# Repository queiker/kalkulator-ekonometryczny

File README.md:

# kalkulator-ekonometryczny
projetk kalkulatora który będzie miał funkcje niedostępne w urządzeniach dostępnych w sklepach
będzie liczył procent składany , będzie miał funkcje prognozy metodą najmniejszych kwadratów

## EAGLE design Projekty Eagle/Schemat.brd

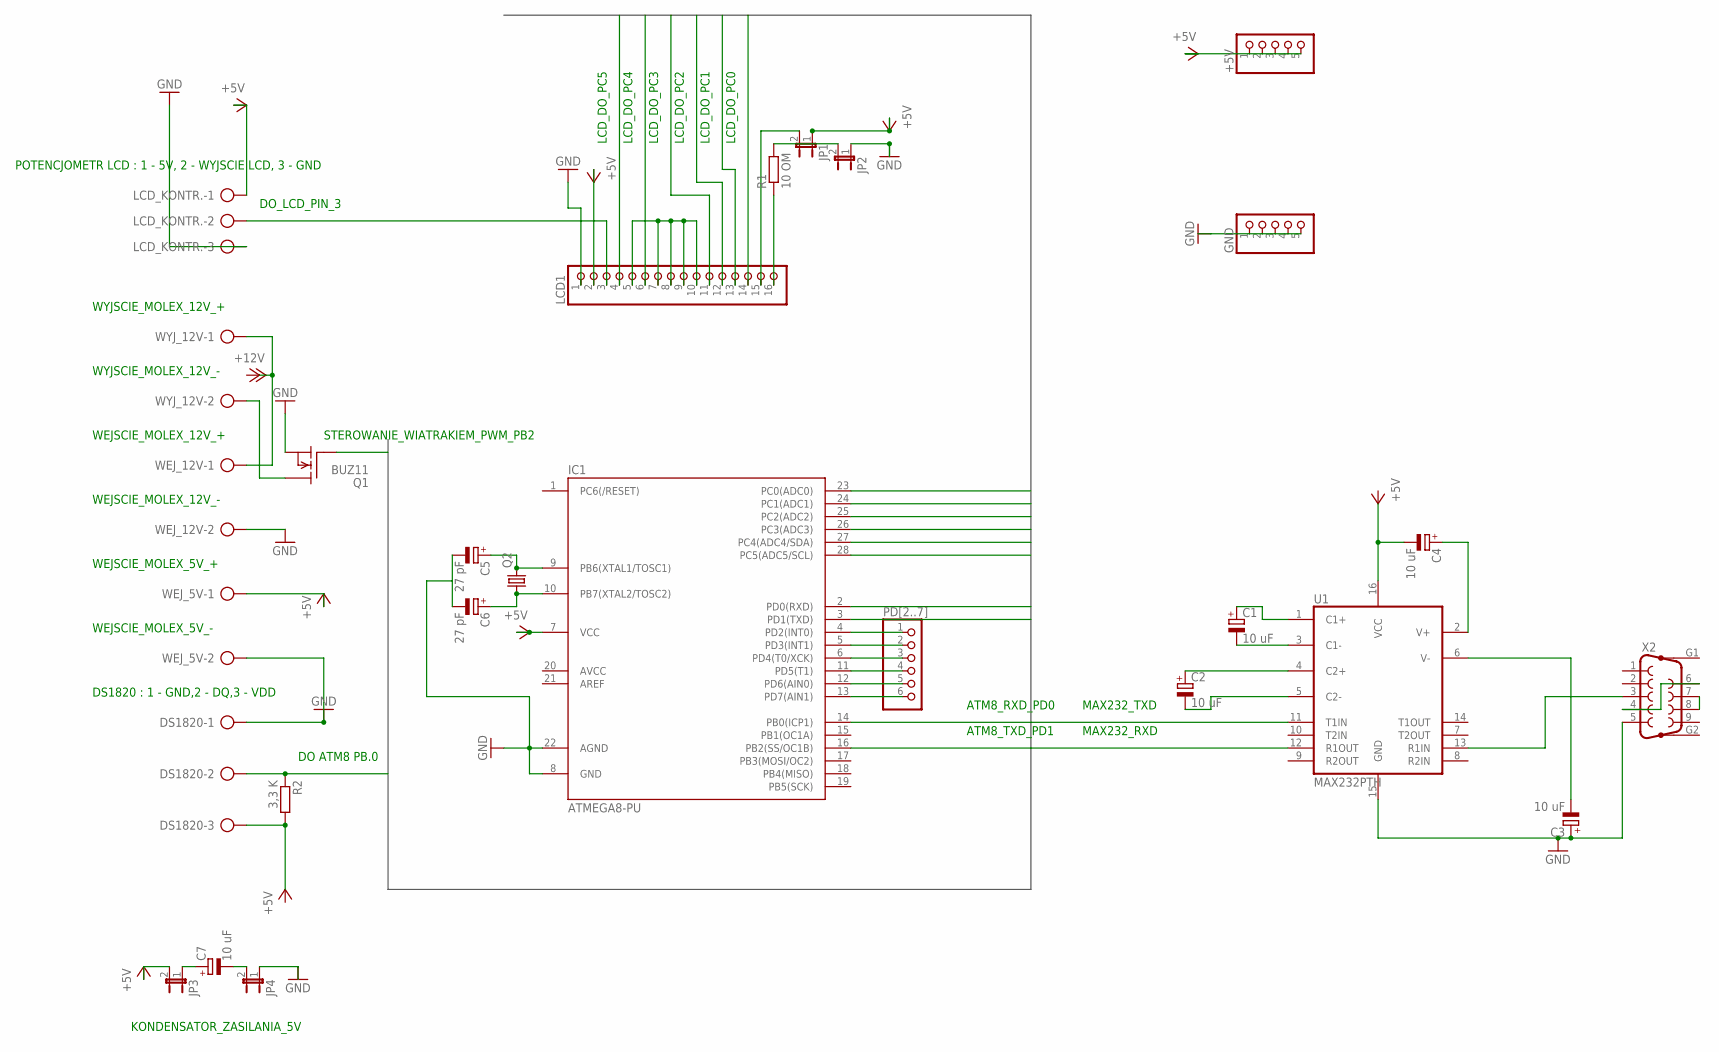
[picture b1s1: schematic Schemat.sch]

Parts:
+5V: PINHD-1X5; 1X05
C1, C2, C3, C4, C7: 10 uF; E5-10,5
C5, C6: 27 pF; E5-10,5
DS1820: AK500/3-H
GND: PINHD-1X5; 1X05
IC1: ATMEGA8-PU; DIL28-3
JP1, JP2, JP3, JP4: JP1E; JP1
LCD1: PINHD-1X16; 1X16
LCD_KONTR.: AK500/3-H
PD[2..7]: PINHD-1X6; 1X06
Q1: BUZ11; TO220
Q2: CRYSTALHC49S; HC49/S
R1: 10 OM; 0207/15
R2: 3,3 K; 0207/15
U1: MAX232PTH; DIL16
WEJ_5V, WEJ_12V: AK500/2-H
WYJ_12V: AK500/2-H
X2: F09HP

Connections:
+5V: +5V.1, +5V.2, +5V.3, +5V.4, +5V.5, IC1.7 (VCC), JP1.1, JP3.2, LCD1.2, LCD_KONTR..1, WEJ_5V.1
GND: C3.+, C5.-, C6.-, DS1820.1, GND.1, GND.2, GND.3, GND.4, GND.5, IC1.8 (GND), IC1.22 (AGND), JP2.1, JP4.1, LCD1.1, LCD_KONTR..3, Q1.3 (S), U1.15 (GND), WEJ_5V.2, WEJ_12V.2, X2.5
unnamed: C1.-, U1.3 (C1-)
unnamed: C1.+, U1.1 (C1+)
unnamed: C2.+, U1.4 (C2+)
unnamed: C2.-, U1.5 (C2-)
unnamed: X2.4, X2.6
unnamed: X2.7, X2.8
unnamed: U1.13 (R1IN), X2.3
unnamed: C4.-, U1.16 (VCC)
unnamed: C3.-, U1.6 (V-)
unnamed: C4.+, U1.2 (V+)
unnamed: C7.+, JP3.1
unnamed: C7.-, JP4.2
unnamed: IC1.4 (PD2(INT0)), PD[2..7].1
unnamed: IC1.5 (PD3(INT1)), PD[2..7].2
unnamed: DS1820.3, R2.2
unnamed: IC1.6 (PD4(T0/XCK)), PD[2..7].3
unnamed: LCD1.3, LCD_KONTR..2
unnamed: WEJ_12V.1, WYJ_12V.1
unnamed: IC1.11 (PD5(T1)), PD[2..7].4
unnamed: Q1.2 (D), WYJ_12V.2
unnamed: LCD1.5, LCD1.7, LCD1.8, LCD1.9, LCD1.10
unnamed: IC1.12 (PD6(AIN0)), PD[2..7].5
unnamed: C5.+, IC1.9 (PB6(XTAL1/TOSC1)), Q2.2
unnamed: IC1.13 (PD7(AIN1)), PD[2..7].6
unnamed: JP1.2, LCD1.15
unnamed: JP2.2, R1.2
unnamed: C6.+, IC1.10 (PB7(XTAL2/TOSC2)), Q2.1
unnamed: LCD1.16, R1.1
PB0: DS1820.2, IC1.14 (PB0(ICP1)), R2.1
PB2: IC1.16 (PB2(SS/OC1B)), Q1.1 (G)
PC0: IC1.23 (PC0(ADC0)), LCD1.14
PC1: IC1.24 (PC1(ADC1)), LCD1.13
PC2: IC1.25 (PC2(ADC2)), LCD1.12
PC3: IC1.26 (PC3(ADC3)), LCD1.11
PC4: IC1.27 (PC4(ADC4/SDA)), LCD1.6
PC5: IC1.28 (PC5(ADC5/SCL)), LCD1.4
PD0: IC1.2 (PD0(RXD)), U1.11 (T1IN)
PD1: IC1.3 (PD1(TXD)), U1.12 (R1OUT)

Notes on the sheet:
MAX232_TXD
MAX232_RXD
WEJSCIE_MOLEX_12V_+
WEJSCIE_MOLEX_12V_-
WEJSCIE_MOLEX_5V_+
WEJSCIE_MOLEX_5V_-
DS1820 : 1 - GND,2 - DQ,3 - VDD
ATM8_RXD_PD0
ATM8_TXD_PD1
POTENCJOMETR LCD : 1 - 5V, 2 - WYJSCIE LCD, 3 - GND
DO ATM8 PB.0
WYJSCIE_MOLEX_12V_+
WYJSCIE_MOLEX_12V_-
STEROWANIE_WIATRAKIEM_PWM_PB2
DO_LCD_PIN_3
LCD_DO_PC5
LCD_DO_PC4
LCD_DO_PC3
LCD_DO_PC2
LCD_DO_PC1
LCD_DO_PC0
KONDENSATOR_ZASILANIA_5V

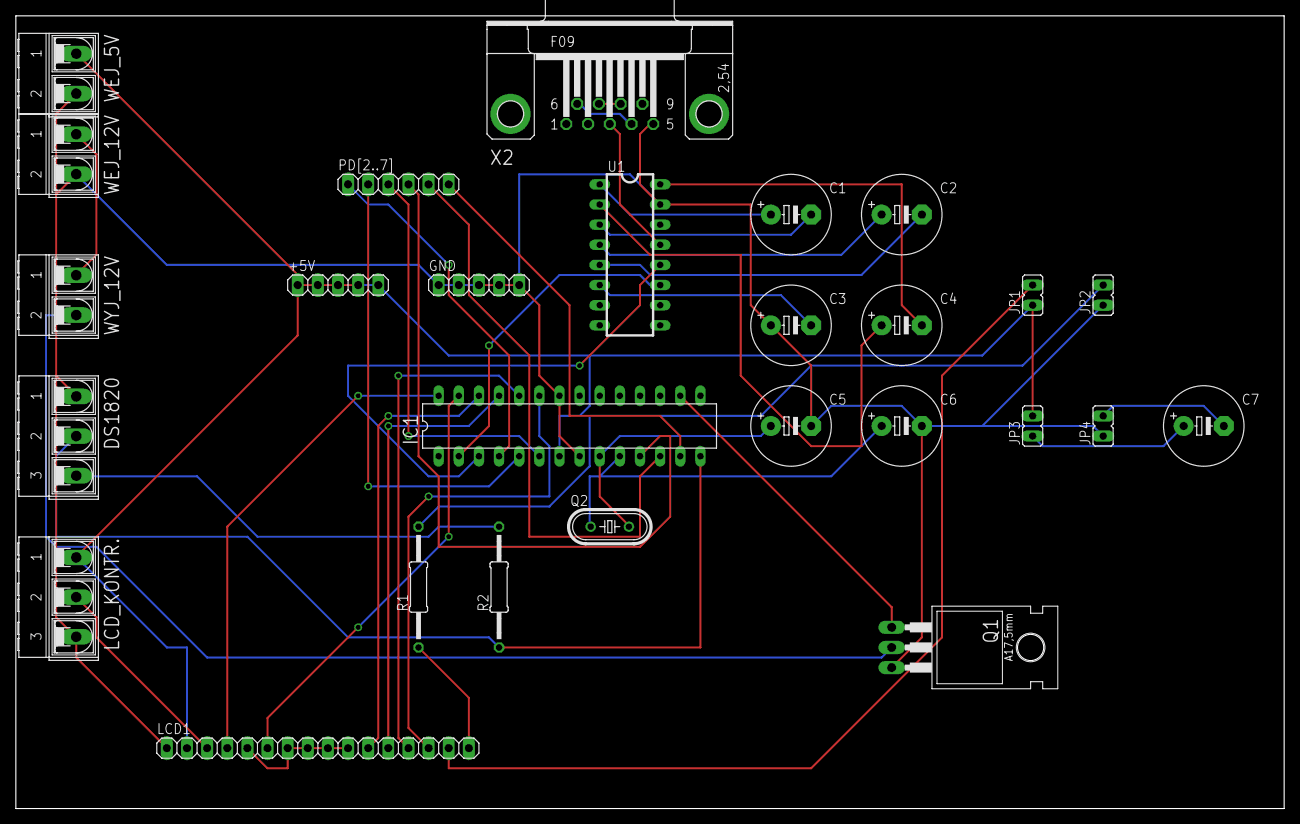
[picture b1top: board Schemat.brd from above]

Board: 2 copper layers, 160.0 x 100.0 mm, 27 parts (0 on the bottom side), 40 nets.

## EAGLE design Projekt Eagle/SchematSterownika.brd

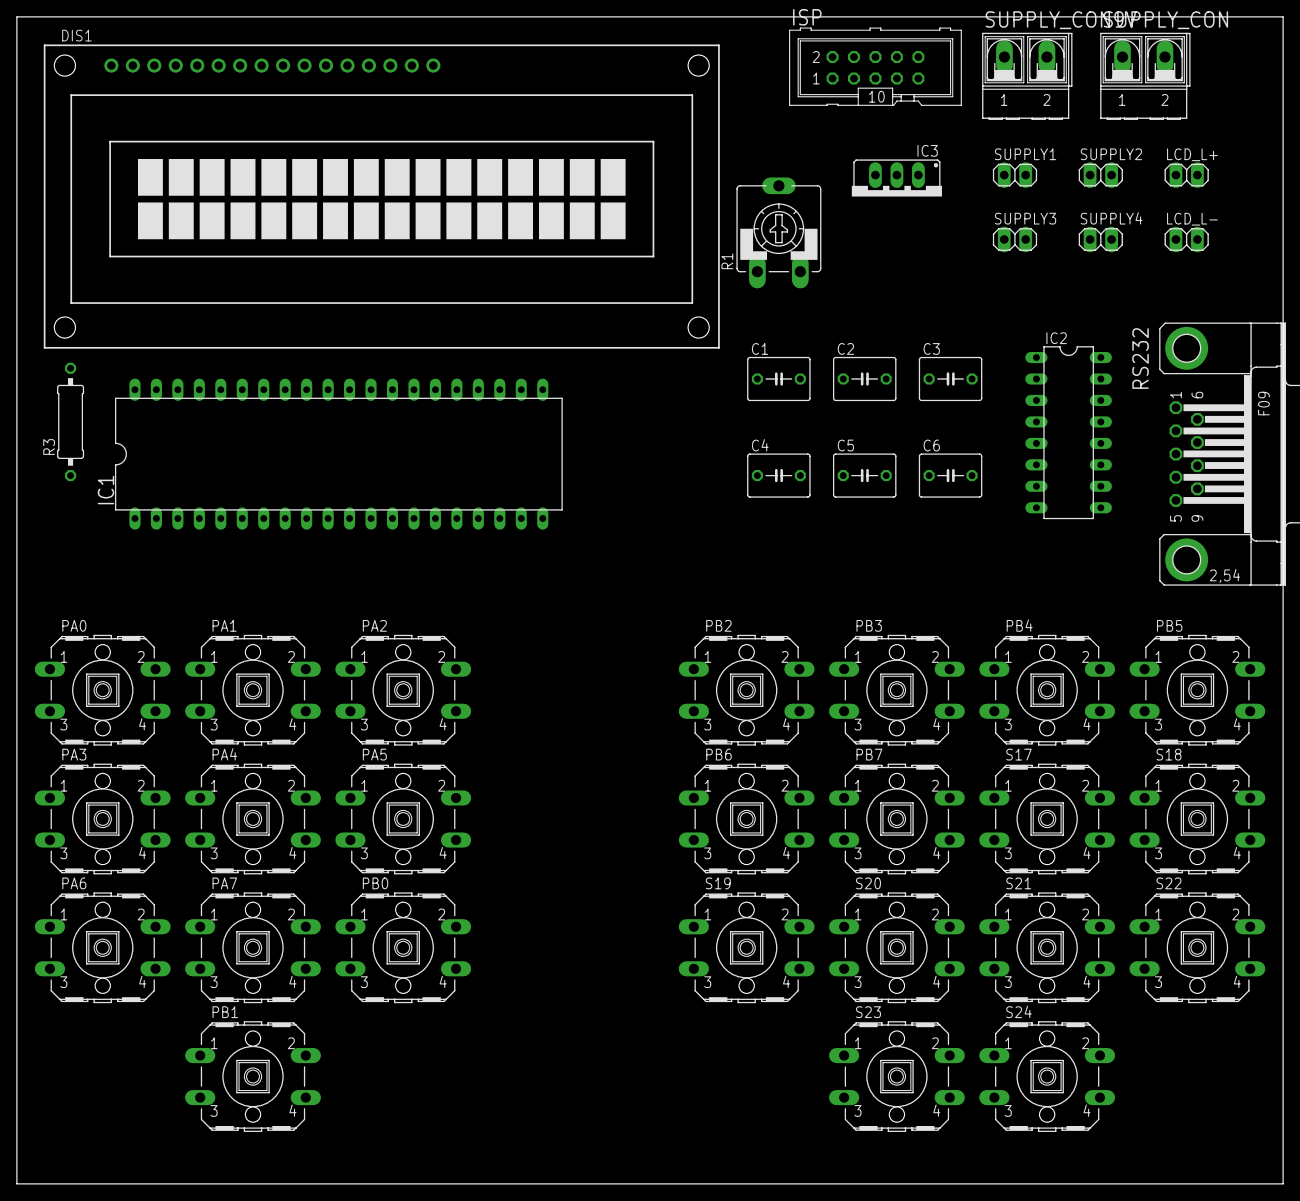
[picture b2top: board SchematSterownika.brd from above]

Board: 2 copper layers, 149.8 x 138.1 mm, 46 parts (0 on the bottom side), 51 nets, no tracks yet.

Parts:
C1, C2, C3, C4, C5, C6: 10uF; C050-050X075
DIS1: TUXGR_16X2_R2
IC1: MEGA32-P; DIL40
IC2: MAX232; DIL16
IC3: 78XXS
ISP: ML10
LCD_L+: JMP_LCD_1; 1X02
LCD_L-: JMP_LCD_2; 1X02
PA0, PA1, PA2, PA3, PA4, PA5, PA6, PA7: B3F-40XX
PB0, PB1, PB2, PB3, PB4, PB5, PB6, PB7: B3F-40XX
R1: CA9V
R3: 10; 0309/12
RS232: F09HP
S17, S18, S19, S20, S21, S22, S23, S24: B3F-40XX
SUPPLY1, SUPPLY2, SUPPLY3, SUPPLY4: SUPPLY 5V; 1X02
SUPPLY_CON, SUPPLY_CON9V: AK500/2-H

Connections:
+5V: C3.2, C5.1, DIS1.2, IC2.16, IC3.OUT, ISP.2, LCD_L+.2, R1.E, SUPPLY1.1, SUPPLY2.1, SUPPLY3.1, SUPPLY4.1, SUPPLY_CON.1
+12V: C6.1, IC3.IN, SUPPLY_CON9V.1
/E: DIS1.6, IC1.17
/GND: IC1.11, IC1.31, IC2.15
/RESET: IC1.9, ISP.5
/RS: DIS1.4, IC1.16
D4: DIS1.11, IC1.18
D5: DIS1.12, IC1.19
D6: DIS1.13, IC1.20
D7: DIS1.14, IC1.21
GND: C2.1, C5.2, C6.2, DIS1.1, DIS1.5, DIS1.7, DIS1.8, DIS1.9, DIS1.10, IC3.GND, ISP.4, ISP.6, ISP.8, ISP.10, LCD_L-.2, PA0.3, PA1.3, PA2.3, PA3.3, PA4.3, PA5.3, PA6.3, PA7.3, PB0.3, PB1.3, PB2.3, PB3.3, PB4.3, PB5.3, PB6.3, PB7.3, R1.A, RS232.5, S17.3, S18.3, S19.3, S20.3, S21.3, S22.3, S23.3, S24.3, SUPPLY1.2, SUPPLY2.2, SUPPLY3.2, SUPPLY4.2, SUPPLY_CON.2, SUPPLY_CON9V.2
unnamed: IC2.13, RS232.3
unnamed: RS232.4, RS232.6
unnamed: RS232.7, RS232.8
unnamed: IC2.14, RS232.2
unnamed: C2.2, IC2.6
unnamed: C3.1, IC2.2
unnamed: C1.1, IC2.1
unnamed: C1.2, IC2.3
unnamed: C4.1, IC2.4
unnamed: C4.2, IC2.5
unnamed: IC1.14, IC2.12
unnamed: IC1.15, IC2.11
unnamed: DIS1.3, R1.S
unnamed: DIS1.16, R3.2
unnamed: DIS1.15, LCD_L+.1
unnamed: LCD_L-.1, R3.1
PA0: IC1.40, PA0.2
PA1: IC1.39, PA1.2
PA2: IC1.38, PA2.2
PA3: IC1.37, PA3.2
PA4: IC1.36, PA4.2
PA5: IC1.35, PA5.2
PA6: IC1.34, PA6.2
PA7: IC1.33, PA7.1
PB0: IC1.1, PB0.1
PB1: IC1.2, PB1.1
PB2: IC1.3, PB2.1
PB3: IC1.4, PB3.1
PB4: IC1.5, PB4.1
PB5: IC1.6, ISP.1, PB5.1
PB6: IC1.7, ISP.9, PB6.1
PB7: IC1.8, ISP.7, PB7.1
PC0: IC1.22, S17.1
PC1: IC1.23, S18.1
PC2: IC1.24, S19.1
PC3: IC1.25, S20.1
PC4: IC1.26, S21.1
PC5: IC1.27, S22.1
PC6: IC1.28, S23.1
PC7: IC1.29, S24.1

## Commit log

2020-10-21 Przeniesieni projektu do github
2020-10-21 trzeba poprawić schemat zamienić goldpiny na przyciski i sprawdzić projekt, płtykę trzeba będzie zrobić jeszcze raz.
2020-11-02 Przerobiłem jumpery na przyciski

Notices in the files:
parts and their libraries:
SparkFun: Licensing: CC v3.0 Share-Alike You are welcome to use this library for commercial purposes.
